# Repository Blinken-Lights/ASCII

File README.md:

# ASCII
ASCII Modular hardware and software repo

I'm designing this collection of modules as an evolution from my original Eurorack modules, which I produced under the name Blinkenlights.

I sell them on Tindie: https://www.tindie.com/stores/nbirch/

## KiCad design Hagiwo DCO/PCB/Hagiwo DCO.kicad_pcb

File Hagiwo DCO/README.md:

Hagiwo DCO schematic / PCB / Panel files

Original schematic and code by @solderstate https://www.instagram.com/solderstate/
Modded by @voll.automat https://www.instagram.com/voll.automat/ https://github.com/luislutz

Please use my modded firmware with different switch logic (to make switch position correspond to LEDs)

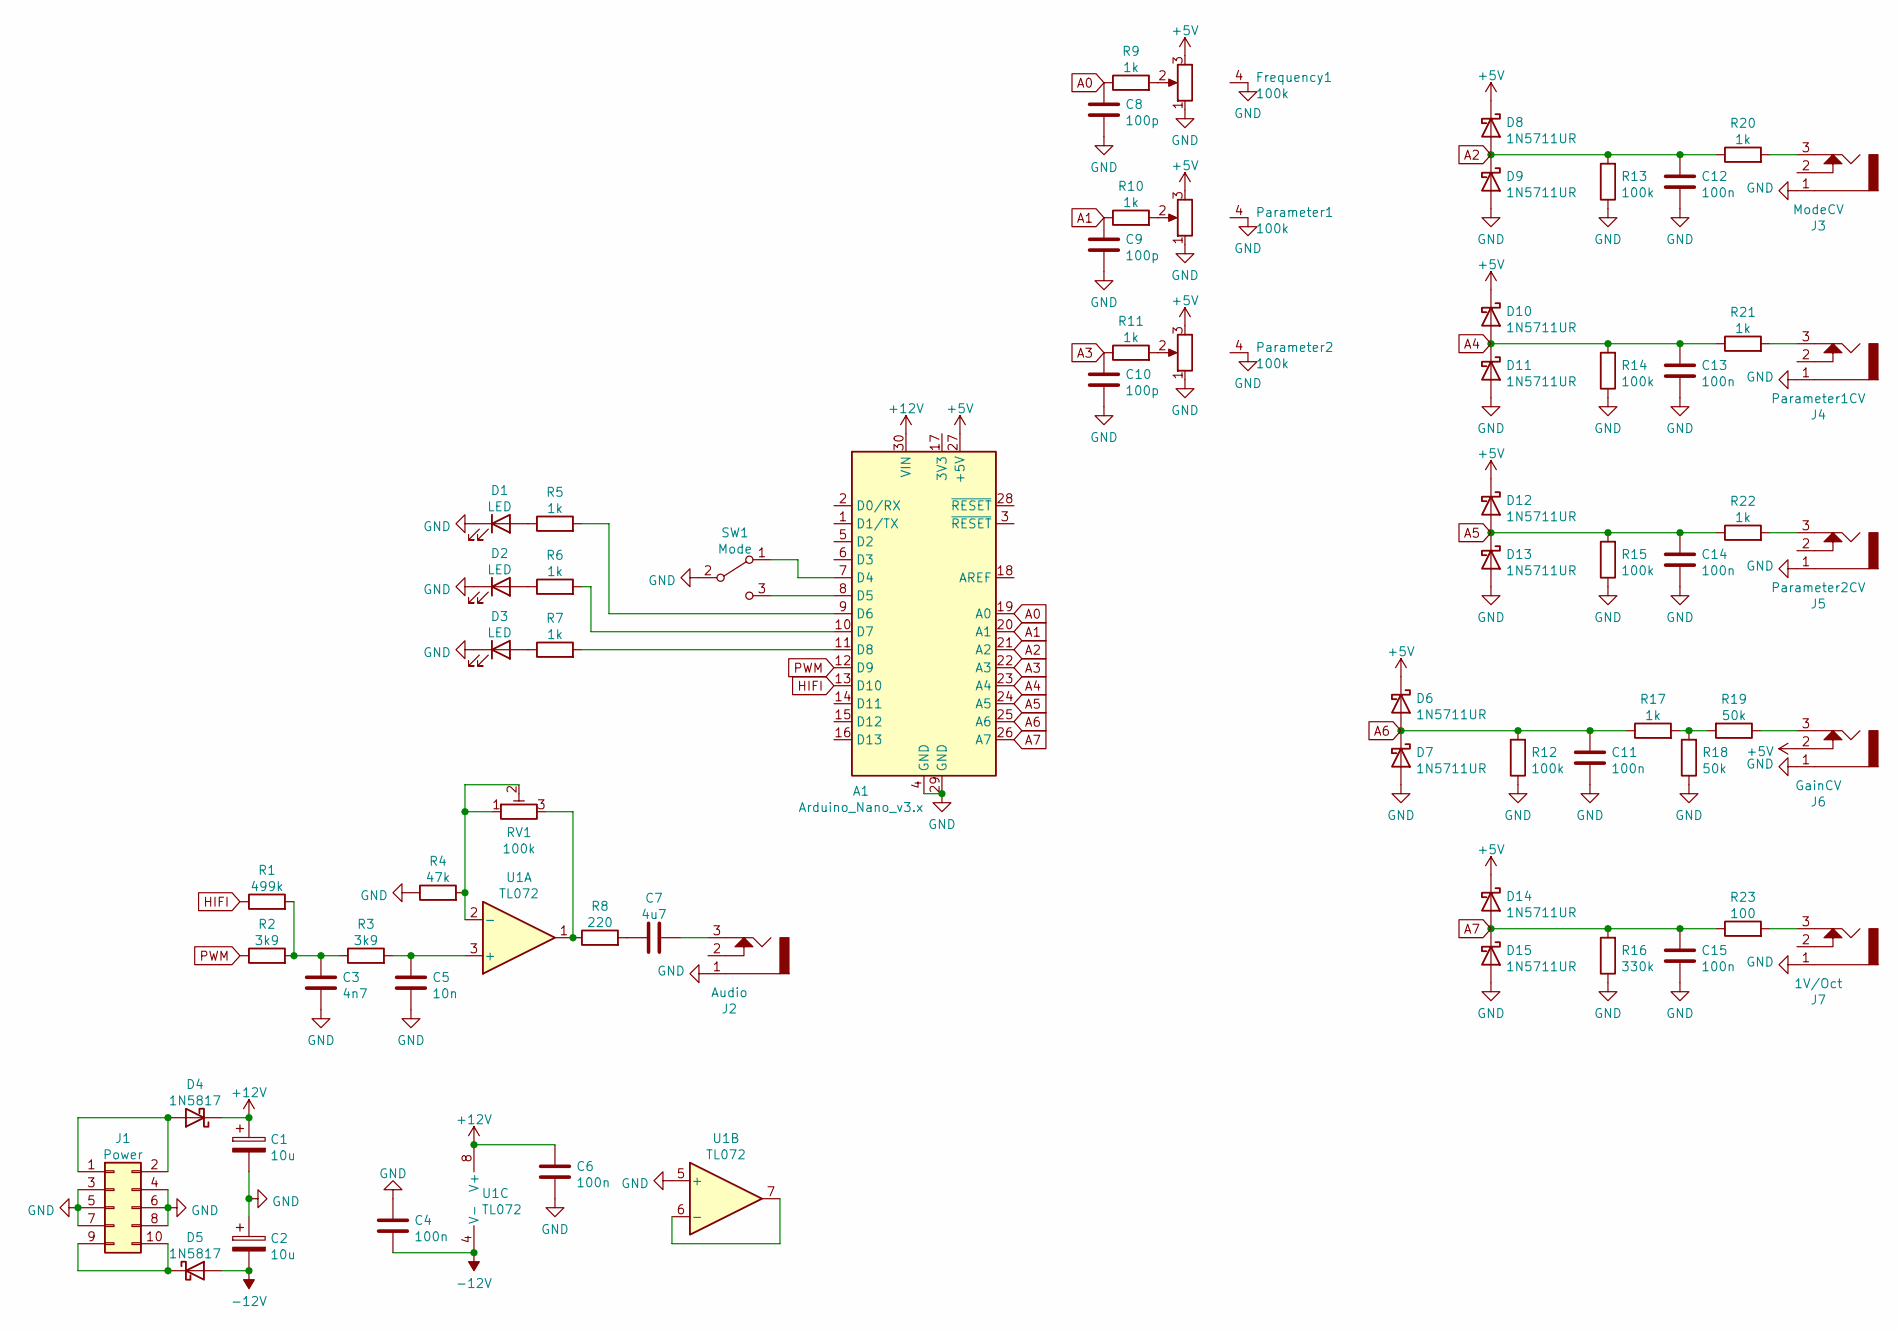
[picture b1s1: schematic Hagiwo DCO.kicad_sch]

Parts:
A1: Arduino_Nano_v3.x; Arduino_Nano
C1, C2: 10u; CP_Radial_D5.0mm_P2.50mm
C3: 4n7; C_0805_2012MetricVal; LCSC C1744
C4, C6, C11, C12, C13, C14, C15: 100n; C_0805_2012MetricVal; LCSC C49678
C5: 10n; C_0805_2012MetricVal; LCSC C1710
C7: 4u7; C_0805_2012MetricVal
C8, C9, C10: 100p; C_0805_2012MetricVal; LCSC C1790
D1, D2, D3: LED; LED_D3.0mm
D4, D5: 1N5817; D_DO-41_SOD81_P10.16mm_Horizontal
D6, D7, D8, D9, D10, D11, D12, D13, D14, D15: 1N5711UR; D_SOD-323_HandSoldering_longerpads; LCSC C151442
Frequency1: 100k; Potentiometer_GND_Alpha_RD901F-40-00D_Single_Vertical_Circu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
J1: Power; PinHeader_2x05_P2.54mm_Vertical
J2: Audio; Thonkiconn
J3: ModeCV; Thonkiconn
J4: Parameter1CV; Thonkiconn
J5: Parameter2CV; Thonkiconn
J6: GainCV; Thonkiconn
J7: 1V/Oct; Thonkiconn
Parameter1, Parameter2: 100k; Potentiometer_GND_Alpha_RD901F-40-00D_Single_Vertical_Circu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
R1: 499k; R_0805_2012MetricValue; LCSC C75783
R2, R3: 3k9; R_0805_2012MetricValue; LCSC C17614
R4: 47k; R_0805_2012MetricValue; LCSC C17713
R5, R6, R7, R9, R10, R11, R17, R20, R21, R22: 1k; R_0805_2012MetricValue; LCSC C17513
R8: 220; R_0805_2012MetricValue; LCSC C17557
R12, R13, R14, R15: 100k; R_0805_2012MetricValue; LCSC C17407
R16: 330k; R_0805_2012MetricValue; LCSC C17629
R18, R19: 50k; R_0805_2012MetricValue; LCSC C63865
R23: 100; R_0805_2012MetricValue; LCSC C17408
RV1: 100k; Potentiometer_Bourns_3296W_Vertical
SW1: Mode; toggle switch
U1: TL072; SO-8_3.9x4.9mm_P1.27mm; LCSC C6961

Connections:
+5V: A1.27 (+5V), D6.1 (K), D8.1 (K), D10.1 (K), D12.1 (K), D14.1 (K), Frequency1.3, J6.2, Parameter1.3, Parameter2.3
+12V: A1.30 (VIN), C1.1, C6.1, D4.1 (K), U1.8 (V+)
-12V: C2.2, C4.2, D5.2 (A), U1.4 (V-)
A0: A1.19 (A0), C8.1, R9.1
A1: A1.20 (A1), C9.1, R10.1
A2: A1.21 (A2), C12.1, D8.2 (A), D9.1 (K), R13.2, R20.1
A3: A1.22 (A3), C10.1, R11.1
A4: A1.23 (A4), C13.1, D10.2 (A), D11.1 (K), R14.2, R21.1
A5: A1.24 (A5), C14.1, D12.2 (A), D13.1 (K), R15.2, R22.1
A6: A1.25 (A6), C11.1, D6.2 (A), D7.1 (K), R12.2, R17.1
A7: A1.26 (A7), C15.1, D14.2 (A), D15.1 (K), R16.2, R23.1
GND: A1.4 (GND), A1.29 (GND), C1.2, C2.1, C3.2, C4.1, C5.2, C6.2, C8.2, C9.2, C10.2, C11.2, C12.2, C13.2, C14.2, C15.2, D1.1 (K), D2.1 (K), D3.1 (K), D7.2 (A), D9.2 (A), D11.2 (A), D13.2 (A), D15.2 (A), Frequency1.1, Frequency1.4 (GND), J1.3, J1.4, J1.5, J1.6, J1.7, J1.8, J2.1, J3.1, J4.1, J5.1, J6.1, J7.1, Parameter1.1, Parameter1.4 (GND), Parameter2.1, Parameter2.4 (GND), R4.1, R12.1, R13.1, R14.1, R15.1, R16.1, R18.1, SW1.2 (B), U1.5 (+)
HIFI: A1.13 (D10), R1.1
unnamed: A1.7 (D4), SW1.1 (A)
unnamed: A1.8 (D5), SW1.3 (C)
unnamed: A1.9 (D6), R5.2
unnamed: A1.10 (D7), R6.2
unnamed: A1.11 (D8), R7.2
unnamed: C3.1, R1.2, R2.2, R3.1
unnamed: C5.1, R3.2, U1.3 (+)
unnamed: C7.1, R8.2
unnamed: C7.2, J2.3
unnamed: D1.2 (A), R5.1
unnamed: D2.2 (A), R6.1
unnamed: D3.2 (A), R7.1
unnamed: D4.2 (A), J1.1, J1.2
unnamed: D5.1 (K), J1.9, J1.10
unnamed: Frequency1.2, R9.2
unnamed: J3.3, R20.2
unnamed: J4.3, R21.2
unnamed: J5.3, R22.2
unnamed: J6.3, R19.1
unnamed: J7.3, R23.2
unnamed: Parameter1.2, R10.2
unnamed: Parameter2.2, R11.2
unnamed: R4.2, RV1.1, RV1.2, U1.2 (-)
unnamed: R8.1, RV1.3, U1.1
unnamed: R17.2, R18.2, R19.2
unnamed: U1.6 (-), U1.7
PWM: A1.12 (D9), R2.1

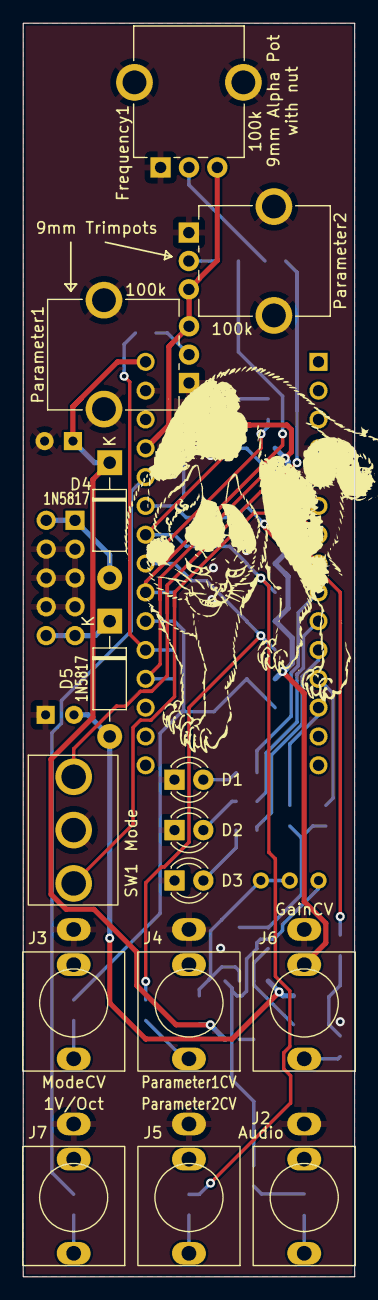
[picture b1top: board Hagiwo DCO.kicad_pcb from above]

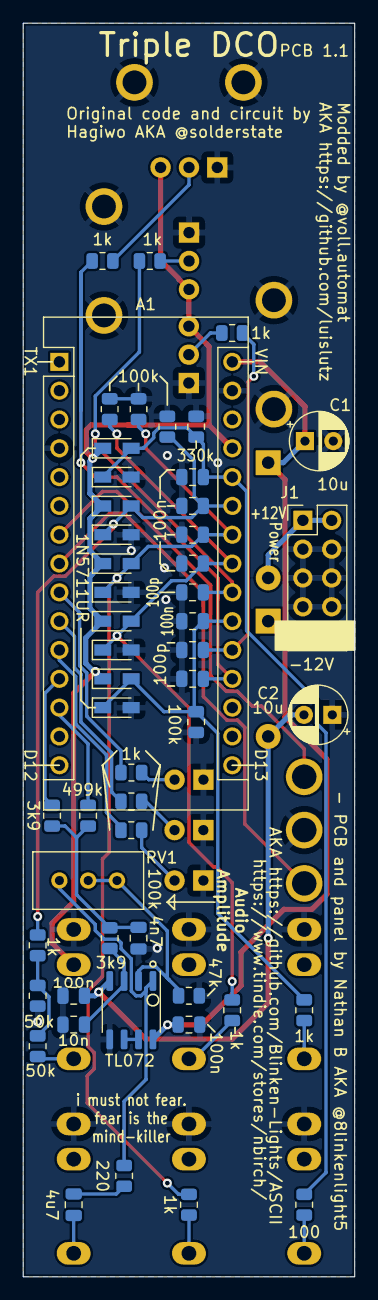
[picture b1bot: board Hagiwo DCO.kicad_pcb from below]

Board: 2 copper layers, 29.2 x 110.5 mm, 67 parts (52 on the bottom side), 40 nets.

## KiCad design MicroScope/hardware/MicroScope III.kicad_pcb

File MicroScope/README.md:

# MicroScope

A small 8HP wide oscilloscope module, similar to my earlier Blinkenlights module of the same name.

This module is based on an STM32 Blue Pill and an RGB 128x128 1.5" SPI OLED screen.

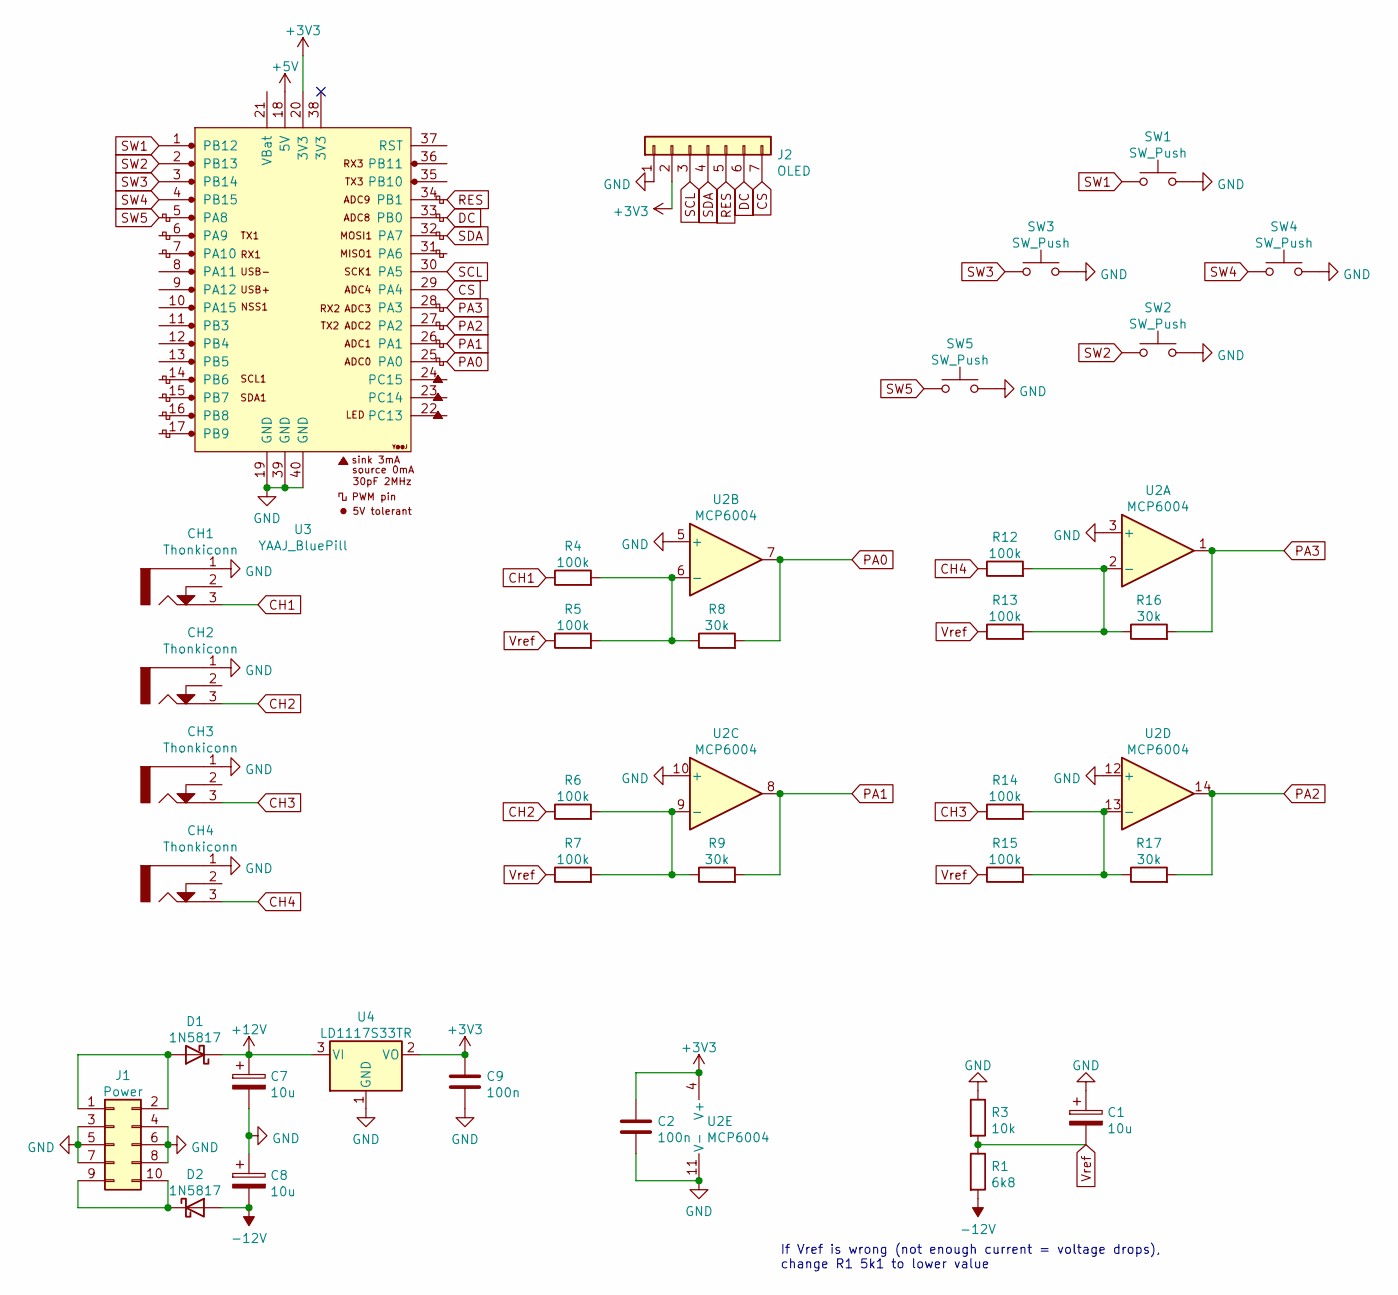
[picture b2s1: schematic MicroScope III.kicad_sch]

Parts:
C1, C7, C8: 10u; CP_Radial_D5.0mm_P2.50mm
C2, C9: 100n; C_0805_2012MetricVal; LCSC C49678
CH1, CH2, CH3, CH4: Thonkiconn
D1, D2: 1N5817; D_DO-41_SOD81_P10.16mm_Horizontal
J1: Power; IDC-Header_2x05_P2.54mm_Vertical
J2: OLED; PinHeader_1x07_P2.54mm_Vertical
R1: 6k8; R_0805_2012MetricValue; LCSC C27834
R3: 10k; R_0805_2012MetricValue; LCSC C17661
R4, R5, R6, R7, R12, R13, R14, R15: 100k; R_0805_2012MetricValue; LCSC C17407
R8, R9, R16, R17: 30k; R_0805_2012MetricValue; LCSC C17621
SW1, SW2, SW3, SW4, SW5: SW_Push; SW_PUSH_6mm
U2: MCP6004; SOIC-14_3.9x8.7mm_P1.27mm; LCSC C7378
U3: YAAJ_BluePill; YAAJ_BluePill_2
U4: LD1117S33TR; SOT-223-3_TabPin2; LCSC C35879

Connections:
+3V3: C2.1, C9.1, J2.2, U2.4 (V+), U3.20 (3V3), U4.2 (VO)
+5V: U3.18 (5V)
+12V: C7.1, D1.1 (K), U4.3 (VI)
-12V: C8.2, D2.2 (A), R1.2
CH1: CH1.3, R4.1
CH2: CH2.3, R6.1
CH3: CH3.3, R14.1
CH4: CH4.3, R12.1
CS: J2.7, U3.29 (PA4)
DC: J2.6, U3.33 (PB0)
GND: C1.1, C2.2, C7.2, C8.1, C9.2, CH1.1, CH2.1, CH3.1, CH4.1, J1.3, J1.4, J1.5, J1.6, J1.7, J1.8, J2.1, R3.1, SW1.2, SW2.2, SW3.2, SW4.2, SW5.2, U2.3 (+), U2.5 (+), U2.10 (+), U2.11 (V-), U2.12 (+), U3.19 (GND), U3.39 (GND), U3.40 (GND), U4.1 (GND)
unnamed: D1.2 (A), J1.1, J1.2
unnamed: D2.1 (K), J1.9, J1.10
unnamed: R4.2, R5.2, R8.1, U2.6 (-)
unnamed: R6.2, R7.2, R9.1, U2.9 (-)
unnamed: R12.2, R13.2, R16.1, U2.2 (-)
unnamed: R14.2, R15.2, R17.1, U2.13 (-)
PA0: R8.2, U2.7, U3.25 (PA0)
PA1: R9.2, U2.8, U3.26 (PA1)
PA2: R17.2, U2.14, U3.27 (PA2)
PA3: R16.2, U2.1, U3.28 (PA3)
RES: J2.5, U3.34 (PB1)
SCL: J2.3, U3.30 (PA5)
SDA: J2.4, U3.32 (PA7)
SW1: SW1.1, U3.1 (PB12)
SW2: SW2.1, U3.2 (PB13)
SW3: SW3.1, U3.3 (PB14)
SW4: SW4.1, U3.4 (PB15)
SW5: SW5.1, U3.5 (PA8)
Vref: C1.2, R1.1, R3.2, R5.1, R7.1, R13.1, R15.1

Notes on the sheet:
If Vref is wrong (not enough current = voltage drops), change R1 5k1 to lower value

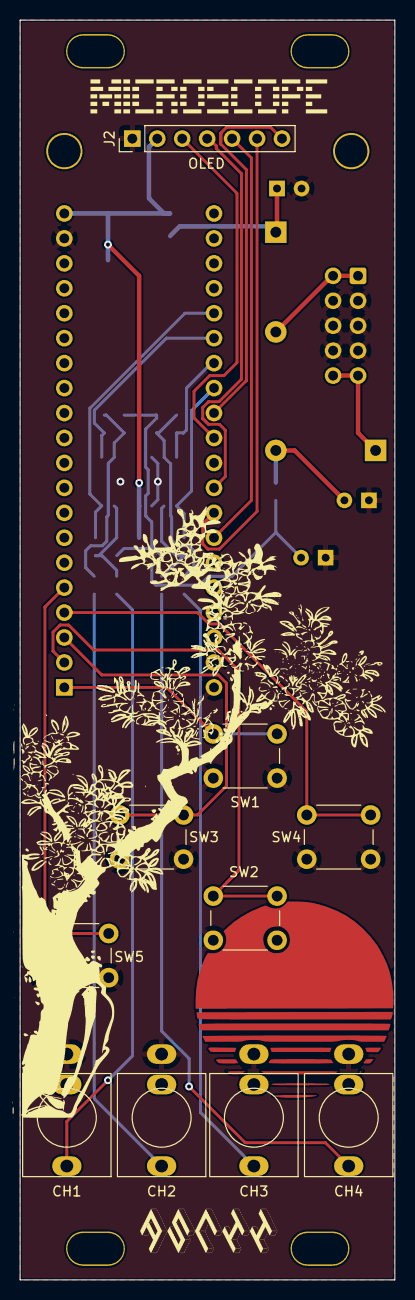
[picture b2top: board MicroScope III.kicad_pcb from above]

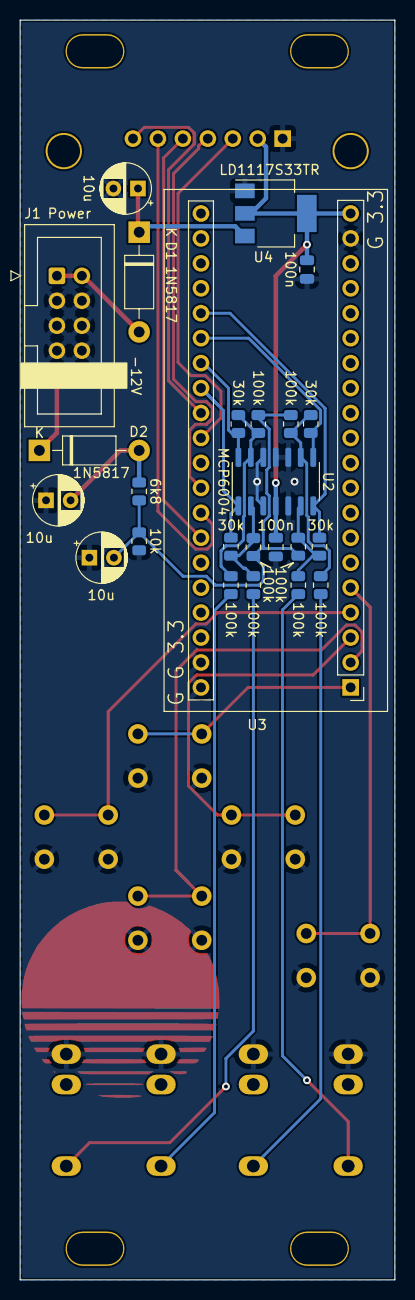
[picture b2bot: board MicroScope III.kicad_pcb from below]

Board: 2 copper layers, 38.2 x 128.3 mm, 35 parts (25 on the bottom side), 29 nets.

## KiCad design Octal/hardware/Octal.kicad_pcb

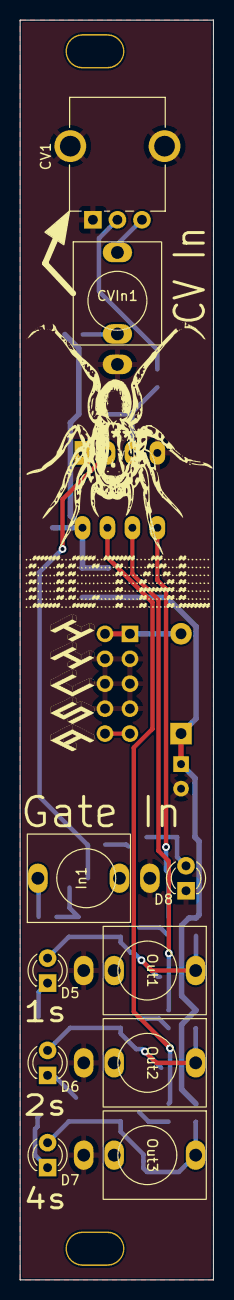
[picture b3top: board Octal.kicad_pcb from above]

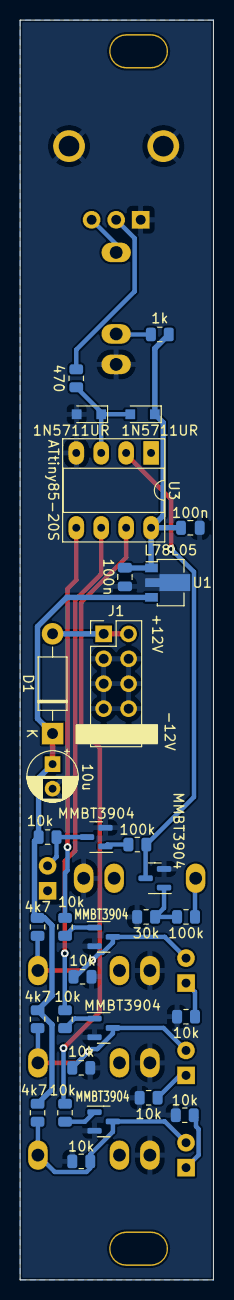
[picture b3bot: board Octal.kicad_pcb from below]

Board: 2 copper layers, 19.7 x 128.3 mm, 42 parts (32 on the bottom side), 26 nets.

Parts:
C1: 10u; CP_Radial_D5.0mm_P2.50mm
C3, C8: 100n; C_0805_2012MetricVal
CV1: 100k; Potentiometer_GND_Alpha_RD901F-40-00D_Single_Vertical_Circu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
CVIn1: Thonkiconn
D1: 1N5817; D_DO-41_SOD81_P10.16mm_Horizontal
D3, D4: 1N5711UR; D_SOD-323_HandSoldering
D5, D6, D7, D8: LED; LED_D3.0mm
In1: Thonkiconn
J1: Power; PinHeader_2x05_P2.54mm_Vertical
Out1, Out2, Out3: Thonkiconn
Q1, Q2, Q3, Q4, Q5: MMBT3904; SOT-23Val
R1, R4, R5, R6, R9, R10, R11, R13, R14, R18: 10k; R_0805_2012MetricValue
R2, R7, R12: 4k7; R_0805_2012MetricValue
R3: 470; R_0805_2012MetricValue
R8: 1k; R_0805_2012MetricValue
R15, R17: 100k; R_0805_2012MetricValue
R16: 30k; R_0805_2012MetricValue
U1: L78L05; SOT-89-3
U3: ATtiny85-20S; DIP-8_W7.62mm_Socket_LongPads

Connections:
+5V: C3.1, C8.1, D3.1 (K), R8.1, U1.1 (OUT), U3.8 (VCC)
+12V: C1.1, D1.1 (K), R2.2, R7.2, R12.2, R18.2, U1.3 (IN)
/Gate In/Input_Pullup: Q4.3 (C), R17.2, U3.2 (XTAL1/PB3)
/Gate Out0/In: R1.1, U3.5 (AREF/PB0)
/Gate Out1/In: R6.1, U3.6 (PB1)
/Gate Out2/In: R11.1, U3.7 (PB2)
CV In: CV1.2, R3.2
GND: C1.2, C3.2, C8.2, CV1.1, CV1.4 (GND), CVIn1.1, D4.2 (A), D8.1 (K), In1.1, J1.3, J1.4, J1.5, J1.6, J1.7, J1.8, Out1.1, Out2.1, Out3.1, Q1.2 (E), Q2.2 (E), Q3.2 (E), Q4.2 (E), Q5.2 (E), R4.1, R5.1, R9.1, R10.1, R13.1, R14.1, R16.1, U1.2 (GND), U3.4 (GND)
unnamed: CV1.3, CVIn1.3
unnamed: CVIn1.2, R8.2
unnamed: D1.2 (A), J1.1, J1.2
unnamed: D3.2 (A), D4.1 (K), R3.1, U3.3 (XTAL2/PB4)
unnamed: D5.1 (K), R5.2
unnamed: D5.2 (A), Out1.3, Q1.3 (C), R2.1, R4.2
unnamed: D6.1 (K), R10.2
unnamed: D6.2 (A), Out2.3, Q2.3 (C), R7.1, R9.2
unnamed: D7.1 (K), R14.2
unnamed: D7.2 (A), Out3.3, Q3.3 (C), R12.1, R13.2
unnamed: D8.2 (A), Q5.3 (C), R18.1
unnamed: In1.3, R15.2
unnamed: J1.9, J1.10
unnamed: Q1.1 (B), R1.2
unnamed: Q2.1 (B), R6.2
unnamed: Q3.1 (B), R11.2
unnamed: Q4.1 (B), R15.1, R16.2
unnamed: Q5.1 (B), R17.1

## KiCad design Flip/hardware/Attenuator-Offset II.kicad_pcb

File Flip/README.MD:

FLIP is a 6 x Attenuverter + Bias utility module.

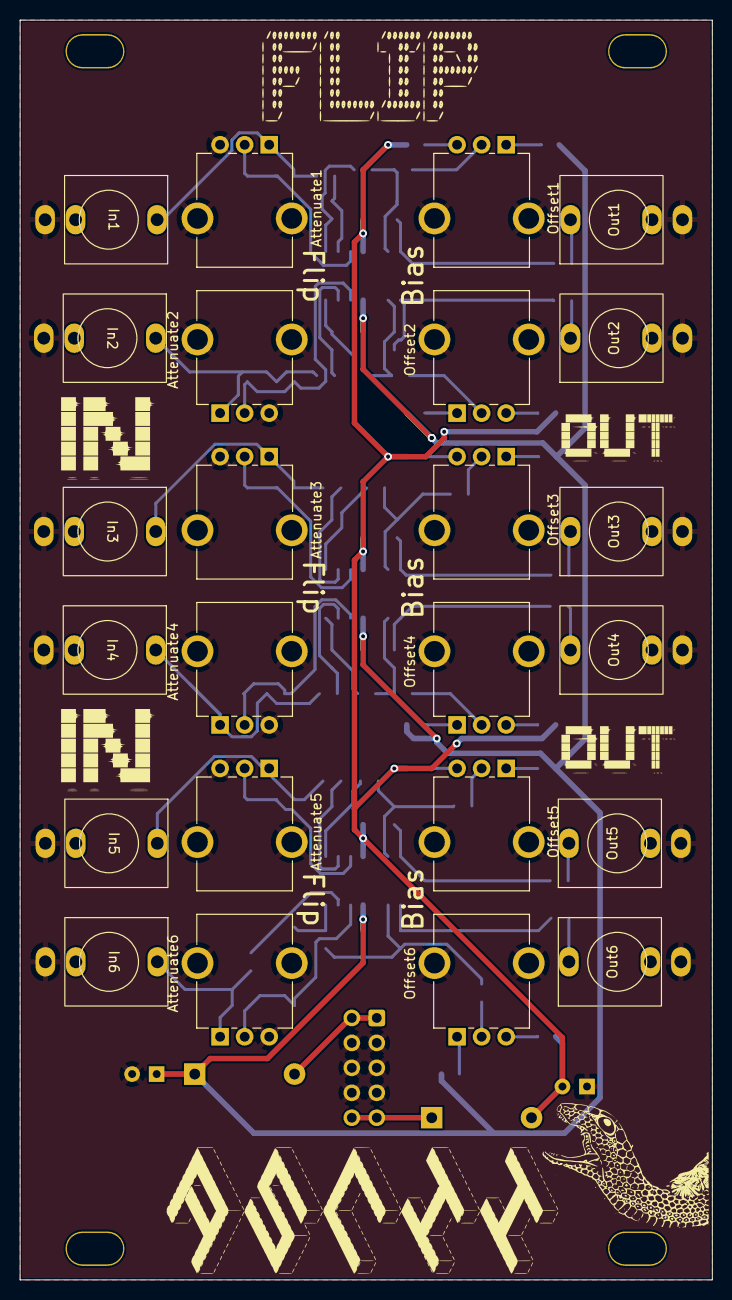
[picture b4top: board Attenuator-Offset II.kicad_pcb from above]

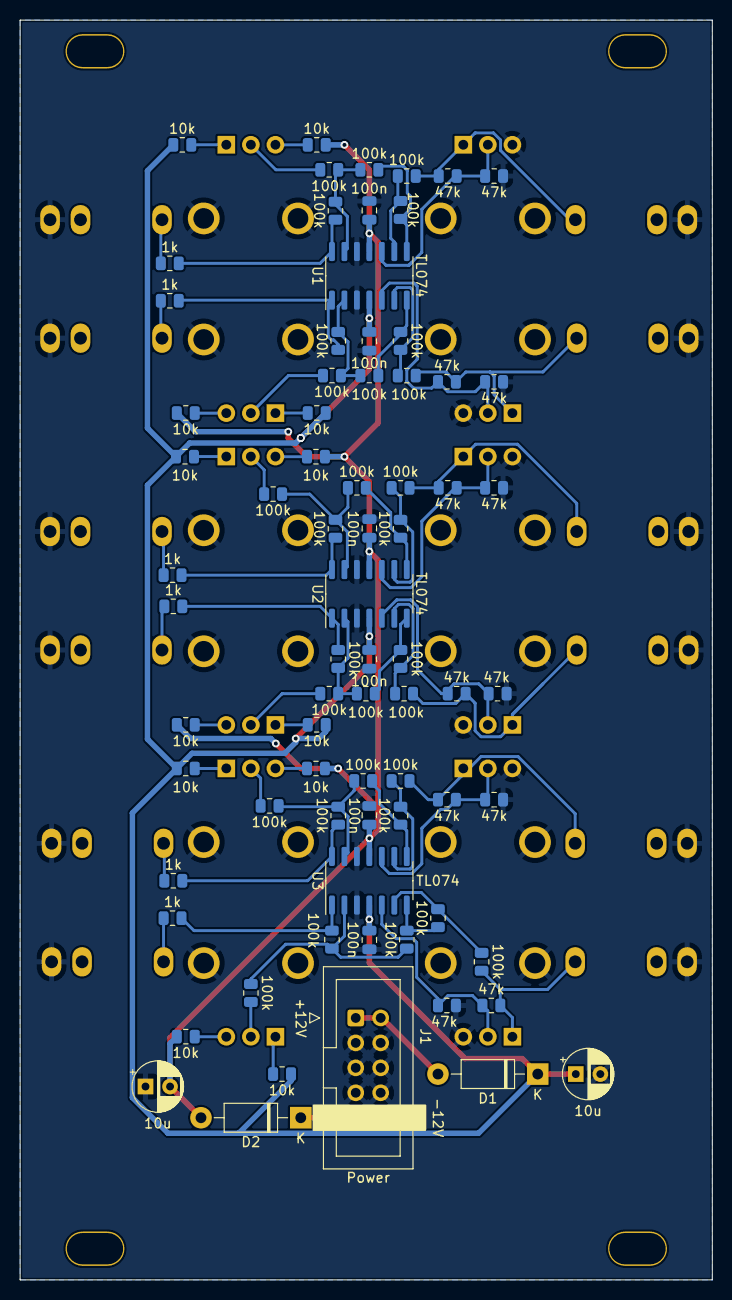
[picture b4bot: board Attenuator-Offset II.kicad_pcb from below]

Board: 2 copper layers, 70.5 x 128.3 mm, 98 parts (74 on the bottom side), 65 nets.

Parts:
Attenuate1, Attenuate2, Attenuate3, Attenuate4, Attenuate5, Attenuate6: 100k; Potentiometer_GND_Alpha_RD901F-40-00D_Single_Vertical_Circu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
C1, C2: 10u; CP_Radial_D5.0mm_P2.50mm
C3, C4, C5, C6, C7, C8: 100n; C_0805_2012MetricVal
D1, D2: 1N5817; D_DO-41_SOD81_P10.16mm_Horizontal
In1, In2, In3, In4, In5, In6: Thonkiconn
J1: Power; IDC-Header_2x05_P2.54mm_Vertical
Offset1, Offset2, Offset3, Offset4, Offset5, Offset6: 100k; Potentiometer_GND_Alpha_RD901F-40-00D_Single_Vertical_Circu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
Out1, Out2, Out3, Out4, Out5, Out6: Thonkiconn
R1, R2, R3, R4, R21, R22, R23, R24, R41, R42, R43, R44: 47k; R_0805_2012MetricValue
R5, R6, R7, R8, R9, R10, R15, R16, R17, R18, R25, R26, R27, R28, R29, R30, R35, R36, R37, R38, R45, R46, R47, R48, R49, R50, R55, R56, R57, R58: 100k; R_0805_2012MetricValue
R11, R12, R13, R14, R31, R32, R33, R34, R51, R52, R53, R54: 10k; R_0805_2012MetricValue
R19, R20, R39, R40, R59, R60: 1k; R_0805_2012MetricValue
U1, U2, U3: TL074; SOIC-14_3.9x8.7mm_P1.27mm

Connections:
+12V: C1.1, C4.1, C6.1, C8.1, D1.1 (K), R11.2, R13.2, R31.2, R33.2, R51.2, R53.2, U1.4 (V+), U2.4 (V+), U3.4 (V+)
-12V: C2.2, C3.2, C5.2, C7.2, D2.2 (A), R12.1, R14.1, R32.1, R34.1, R52.1, R54.1, U1.11 (V-), U2.11 (V-), U3.11 (V-)
GND: Attenuate1.3, Attenuate1.4 (GND), Attenuate2.3, Attenuate2.4 (GND), Attenuate3.3, Attenuate3.4 (GND), Attenuate4.3, Attenuate4.4 (GND), Attenuate5.3, Attenuate5.4 (GND), Attenuate6.3, Attenuate6.4 (GND), C1.2, C2.1, C3.1, C4.2, C5.1, C6.2, C7.1, C8.2, In1.1, In2.1, In3.1, In4.1, In5.1, In6.1, J1.3, J1.4, J1.5, J1.6, J1.7, J1.8, Offset1.4 (GND), Offset2.4 (GND), Offset3.4 (GND), Offset4.4 (GND), Offset5.4 (GND), Offset6.4 (GND), Out1.1, Out2.1, Out3.1, Out4.1, Out5.1, Out6.1, R1.2, R3.2, R21.2, R23.2, R41.2, R43.2, U1.3 (+), U1.12 (+), U2.3 (+), U2.12 (+), U3.3 (+), U3.12 (+)
unnamed: Attenuate1.1, In1.3, R2.1, R5.1
unnamed: Attenuate1.2, R1.1, R2.2, U1.10 (+)
unnamed: Attenuate2.1, In2.3, R4.1, R6.1
unnamed: Attenuate2.2, R3.1, R4.2, U1.5 (+)
unnamed: Attenuate3.1, In3.3, R22.1, R25.1
unnamed: Attenuate3.2, R21.1, R22.2, U2.10 (+)
unnamed: Attenuate4.1, In4.3, R24.1, R26.1
unnamed: Attenuate4.2, R23.1, R24.2, U2.5 (+)
unnamed: Attenuate5.1, In5.3, R42.1, R45.1
unnamed: Attenuate5.2, R41.1, R42.2, U3.10 (+)
unnamed: Attenuate6.1, In6.3, R44.1, R46.1
unnamed: Attenuate6.2, R43.1, R44.2, U3.5 (+)
unnamed: D1.2 (A), J1.1, J1.2
unnamed: D2.1 (K), J1.9, J1.10
unnamed: Offset1.1, R11.1
unnamed: Offset1.2, R15.1
unnamed: Offset1.3, R12.2
unnamed: Offset2.1, R13.1
unnamed: Offset2.2, R16.1
unnamed: Offset2.3, R14.2
unnamed: Offset3.1, R31.1
unnamed: Offset3.2, R35.1
unnamed: Offset3.3, R32.2
unnamed: Offset4.1, R33.1
unnamed: Offset4.2, R36.1
unnamed: Offset4.3, R34.2
unnamed: Offset5.1, R51.1
unnamed: Offset5.2, R55.1
unnamed: Offset5.3, R52.2
unnamed: Offset6.1, R53.1
unnamed: Offset6.2, R56.1
unnamed: Offset6.3, R54.2
unnamed: Out1.3, R19.2
unnamed: Out2.3, R20.2
unnamed: Out3.3, R39.2
unnamed: Out4.3, R40.2
unnamed: Out5.3, R59.2
unnamed: Out6.3, R60.2
unnamed: R5.2, R7.1, U1.9 (-)
unnamed: R6.2, R8.1, U1.6 (-)
unnamed: R7.2, R9.1, U1.8
unnamed: R8.2, R10.1, U1.7
unnamed: R10.2, R16.2, R17.1, U1.2 (-)
unnamed: R9.2, R15.2, R18.1, U1.13 (-)
unnamed: R17.2, R20.1, U1.1
unnamed: R18.2, R19.1, U1.14
unnamed: R25.2, R27.1, U2.9 (-)
unnamed: R26.2, R28.1, U2.6 (-)
unnamed: R27.2, R29.1, U2.8
unnamed: R28.2, R30.1, U2.7
unnamed: R29.2, R35.2, R38.1, U2.13 (-)
unnamed: R30.2, R36.2, R37.1, U2.2 (-)
unnamed: R37.2, R40.1, U2.1
unnamed: R38.2, R39.1, U2.14
unnamed: R45.2, R47.1, U3.9 (-)
unnamed: R46.2, R48.1, U3.6 (-)
unnamed: R47.2, R49.1, U3.8
unnamed: R48.2, R50.1, U3.7
unnamed: R49.2, R55.2, R58.1, U3.13 (-)
unnamed: R50.2, R56.2, R57.1, U3.2 (-)
unnamed: R57.2, R60.1, U3.1
unnamed: R58.2, R59.1, U3.14

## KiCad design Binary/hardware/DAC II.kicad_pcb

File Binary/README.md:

# Binary

This module is a 1V/Oct CV generator (max 5.33V) that takes several gate inputs and spits out 1V/Oct CV quantised by several choices of scale.

It's split into 2 identical channels. Each channel takes 6 gates, split into 3 for 'note' and 3 for 'octave'. Each group of 3 are combined as binary digits to derive a number from 0-7. The 'note' number corresponds to a degree on a scale. The 'octave' number.. defines the octave :)

A single potentiometer chooses the scale used on both channels, so both channels should sound fairly good together.

When any of the gates on a channel changes state, a trigger output goes HIGH, which can be used to EG trigger an envelope generator. You don't need to use all of the 12 possible gates - unconnected gates are considered LOW.

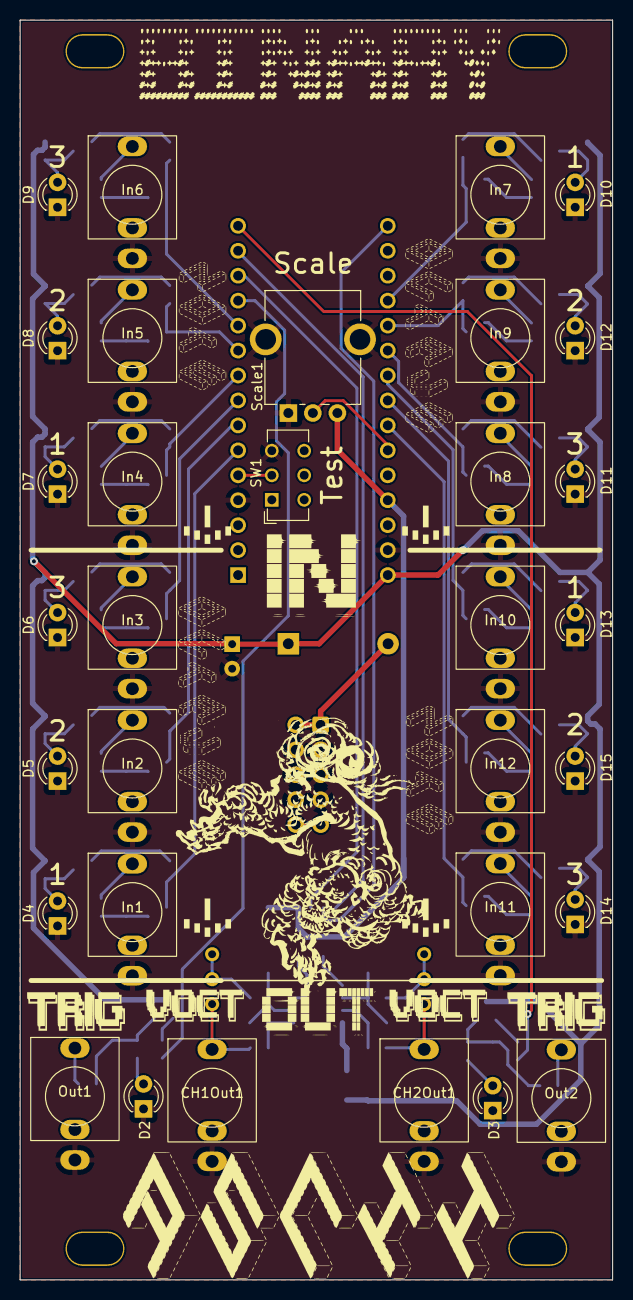
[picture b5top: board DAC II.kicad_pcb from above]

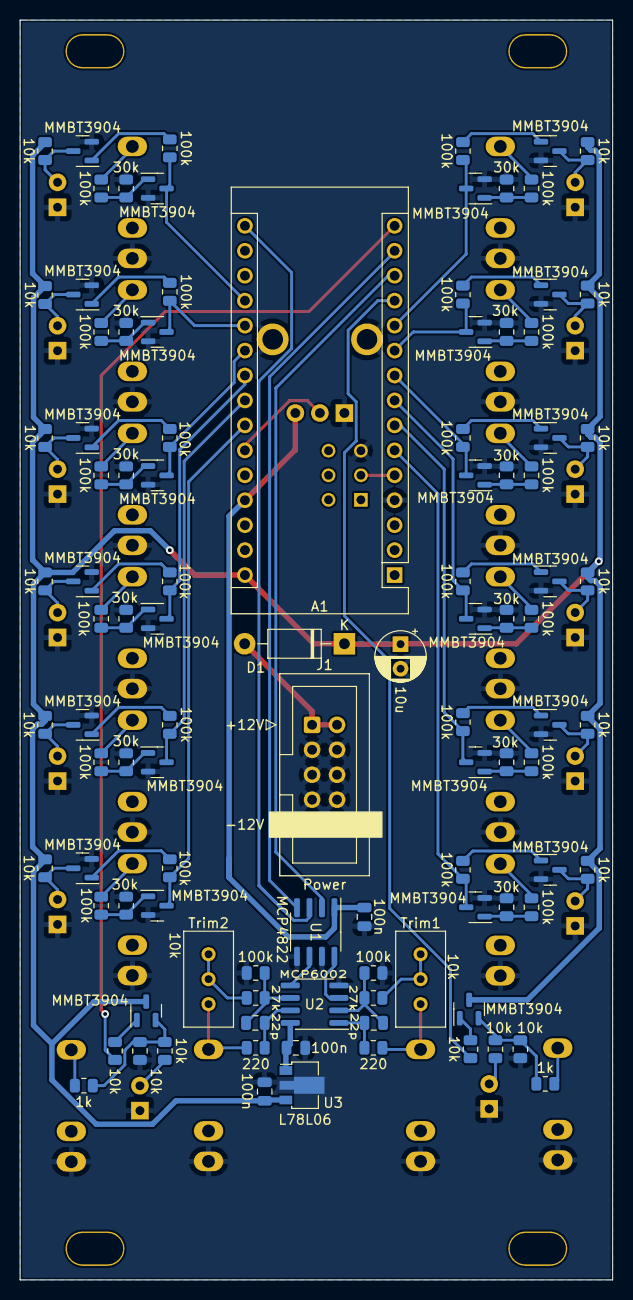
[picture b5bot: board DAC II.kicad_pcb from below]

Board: 2 copper layers, 60.3 x 128.3 mm, 134 parts (102 on the bottom side), 91 nets.

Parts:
A1: Arduino_Nano_v3.x; Arduino_Nano
C1: 10u; CP_Radial_D5.0mm_P2.50mm
C2, C3, C4: 100n; C_0805_2012MetricVal
C6, C7: 22p; C_0805_2012MetricVal
CH1Out1, CH2Out1: Thonkiconn
D1: 1N5817; D_DO-41_SOD81_P10.16mm_Horizontal
D2, D3, D4, D5, D6, D7, D8, D9, D10, D11, D12, D13, D14, D15: LED; LED_D3.0mm
In1, In2, In3, In4, In5, In6, In7, In8, In9, In10, In11, In12: Thonkiconn
J1: Power; IDC-Header_2x05_P2.54mm_Vertical
Out1, Out2: Thonkiconn
Q1, Q2, Q3, Q4, Q5, Q6, Q7, Q8, Q9, Q10, Q11, Q12, Q13, Q14, Q15, Q16, Q17, Q18, Q19, Q20, Q21, Q22, Q23, Q24, Q25, Q26: MMBT3904; SOT-23Val
R1, R2, R15, R17, R19, R21, R23, R25, R27, R29, R31, R33, R35, R37, R39, R41, R43, R45, R47, R49, R51, R53, R55, R57, R59, R61: 100k; R_0805_2012MetricValue
R3, R4: 27k; R_0805_2012MetricValue
R5, R6: 220; R_0805_2012MetricValue
R7, R8, R9, R11, R12, R13, R18, R22, R26, R30, R34, R38, R42, R46, R50, R54, R58, R62: 10k; R_0805_2012MetricValue
R10, R14: 1k; R_0805_2012MetricValue
R16, R20, R24, R28, R32, R36, R40, R44, R48, R52, R56, R60: 30k; R_0805_2012MetricValue
SW1: Test; SW_CuK_JS202011CQN_DPDT_Straight
Scale1: 100k; Potentiometer_GND_Alpha_RD901F-40-00D_Single_Vertical_Circu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
Trim1, Trim2: 10k; Potentiometer_Bourns_3296W_Vertical
U1: MCP4822; SOIC-8_3.9x4.9mm_P1.27mm
U2: MCP6002; SOIC-8_3.9x4.9mm_P1.27mm
U3: L78L06; SOT-89-3

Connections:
+5V: A1.27 (+5V), C2.1, Scale1.3, U1.1 (Vdd)
+6V: C4.1, U2.8 (V+), U3.1 (OUT)
+12V: A1.30 (VIN), C1.1, C3.1, D1.1 (K), Q1.3 (C), Q2.3 (C), R18.2, R22.2, R26.2, R30.2, R34.2, R38.2, R42.2, R46.2, R50.2, R54.2, R58.2, R62.2, U3.3 (IN)
CS: A1.13 (D10), U1.2 (~CS)
GND: A1.4 (GND), A1.29 (GND), C1.2, C2.2, C3.2, C4.2, CH1Out1.1, CH2Out1.1, D2.1 (K), D3.1 (K), D4.1 (K), D5.1 (K), D6.1 (K), D7.1 (K), D8.1 (K), D9.1 (K), D10.1 (K), D11.1 (K), D12.1 (K), D13.1 (K), D14.1 (K), D15.1 (K), In1.1, In2.1, In3.1, In4.1, In5.1, In6.1, In7.1, In8.1, In9.1, In10.1, In11.1, In12.1, J1.3, J1.4, J1.5, J1.6, J1.7, J1.8, Out1.1, Out2.1, Q3.2 (E), Q4.2 (E), Q5.2 (E), Q6.2 (E), Q7.2 (E), Q8.2 (E), Q9.2 (E), Q10.2 (E), Q11.2 (E), Q12.2 (E), Q13.2 (E), Q14.2 (E), Q15.2 (E), Q16.2 (E), Q17.2 (E), Q18.2 (E), Q19.2 (E), Q20.2 (E), Q21.2 (E), Q22.2 (E), Q23.2 (E), Q24.2 (E), Q25.2 (E), Q26.2 (E), R1.1, R2.1, R8.1, R12.1, R16.1, R20.1, R24.1, R28.1, R32.1, R36.1, R40.1, R44.1, R48.1, R52.1, R56.1, R60.1, SW1.3 (C), Scale1.1, Scale1.4 (GND), U1.5 (~LDAC), U1.7 (Vss), U2.4 (V-), U3.2 (GND)
MOSI: A1.14 (D11), U1.4 (SDI)
NOT0-1: A1.9 (D6), Q9.3 (C), R29.2
NOT0-2: A1.22 (A3), Q21.3 (C), R53.2
NOT1-1: A1.10 (D7), Q11.3 (C), R33.2
NOT1-2: A1.23 (A4), Q25.3 (C), R61.2
NOT2-1: A1.11 (D8), Q13.3 (C), R37.2
NOT2-2: A1.24 (A5), Q23.3 (C), R57.2
unnamed: A1.5 (D2), SW1.2 (B)
unnamed: A1.25 (A6), Scale1.2
unnamed: C6.1, R1.2, R3.1, U2.6 (-)
unnamed: C6.2, R5.1, U2.7
unnamed: C7.1, R2.2, R4.1, U2.2 (-)
unnamed: C7.2, R6.1, U2.1
unnamed: CH1Out1.3, R6.2, Trim1.3
unnamed: CH2Out1.3, R5.2, Trim2.3
unnamed: D1.2 (A), J1.1, J1.2
unnamed: D2.2 (A), R9.1
unnamed: D3.2 (A), R13.1
unnamed: D4.2 (A), Q4.3 (C), R18.1
unnamed: D5.2 (A), Q6.3 (C), R22.1
unnamed: D6.2 (A), Q8.3 (C), R26.1
unnamed: D7.2 (A), Q10.3 (C), R30.1
unnamed: D8.2 (A), Q12.3 (C), R34.1
unnamed: D9.2 (A), Q14.3 (C), R38.1
unnamed: D10.2 (A), Q16.3 (C), R42.1
unnamed: D11.2 (A), Q18.3 (C), R46.1
unnamed: D12.2 (A), Q20.3 (C), R50.1
unnamed: D13.2 (A), Q22.3 (C), R54.1
unnamed: D14.2 (A), Q24.3 (C), R58.1
unnamed: D15.2 (A), Q26.3 (C), R62.1
unnamed: In1.3, R15.2
unnamed: In2.3, R19.2
unnamed: In3.3, R23.2
unnamed: In4.3, R27.2
unnamed: In5.3, R31.2
unnamed: In6.3, R35.2
unnamed: In7.3, R39.2
unnamed: In8.3, R43.2
unnamed: In9.3, R47.2
unnamed: In10.3, R51.2
unnamed: In11.3, R55.2
unnamed: In12.3, R59.2
unnamed: J1.9, J1.10
unnamed: Out1.3, R10.1
unnamed: Out2.3, R14.1
unnamed: Q1.1 (B), R7.2
unnamed: Q1.2 (E), R8.2, R9.2, R10.2
unnamed: Q2.1 (B), R11.2
unnamed: Q2.2 (E), R12.2, R13.2, R14.2
unnamed: Q3.1 (B), R15.1, R16.2
unnamed: Q4.1 (B), R17.1
unnamed: Q5.1 (B), R19.1, R20.2
unnamed: Q6.1 (B), R21.1
unnamed: Q7.1 (B), R23.1, R24.2
unnamed: Q8.1 (B), R25.1
unnamed: Q9.1 (B), R27.1, R28.2
unnamed: Q10.1 (B), R29.1
unnamed: Q11.1 (B), R31.1, R32.2
unnamed: Q12.1 (B), R33.1
unnamed: Q13.1 (B), R35.1, R36.2
unnamed: Q14.1 (B), R37.1
unnamed: Q15.1 (B), R39.1, R40.2
unnamed: Q16.1 (B), R41.1
unnamed: Q17.1 (B), R43.1, R44.2
unnamed: Q18.1 (B), R45.1
unnamed: Q19.1 (B), R47.1, R48.2
unnamed: Q20.1 (B), R49.1
unnamed: Q21.1 (B), R51.1, R52.2
unnamed: Q22.1 (B), R53.1
unnamed: Q23.1 (B), R55.1, R56.2
unnamed: Q24.1 (B), R57.1
unnamed: Q25.1 (B), R59.1, R60.2
unnamed: Q26.1 (B), R61.1
unnamed: R3.2, Trim2.1, Trim2.2
unnamed: R4.2, Trim1.1, Trim1.2
unnamed: U1.6 (VB), U2.5 (+)
unnamed: U1.8 (VA), U2.3 (+)
OCT0-1: A1.6 (D3), Q3.3 (C), R17.2
OCT0-2: A1.19 (A0), Q15.3 (C), R41.2
OCT1-1: A1.7 (D4), Q5.3 (C), R21.2
OCT1-2: A1.20 (A1), Q19.3 (C), R49.2
OCT2-1: A1.8 (D5), Q7.3 (C), R25.2
OCT2-2: A1.21 (A2), Q17.3 (C), R45.2
SCK: A1.16 (D13), U1.3 (SCK)
Trig1: A1.12 (D9), R7.1
Trig2: A1.15 (D12), R11.1
